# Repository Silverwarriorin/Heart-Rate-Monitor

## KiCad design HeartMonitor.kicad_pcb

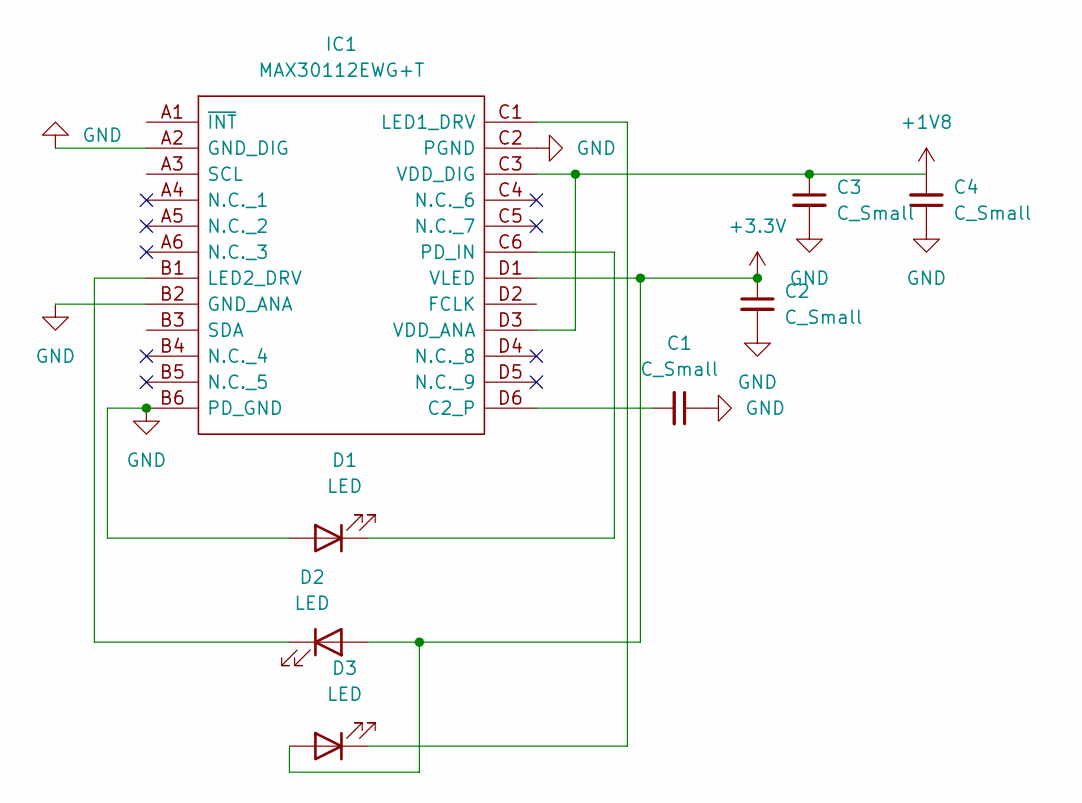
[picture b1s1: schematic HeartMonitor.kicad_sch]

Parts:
C1, C2, C3, C4: C_Small; C_0603_1608Metric_Pad1.08x0.95mm_HandSolder
D1, D2, D3: LED; D_0201_0603Metric
IC1: MAX30112EWG+T; BGA24C40P6X4_277X197X69; Mouser Part Number 700-MAX30112EWG+T

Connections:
+1V8: C3.1, C4.2, IC1.C3 (VDD_DIG), IC1.D3 (VDD_ANA)
+3V3: C2.1, D2.2 (A), D3.2 (A), IC1.D1 (VLED)
GND: C1.1, C2.2, C3.2, C4.1, D1.2 (A), IC1.A2 (GND_DIG), IC1.B2 (GND_ANA), IC1.B6 (PD_GND), IC1.C2 (PGND)
unnamed: D2.1 (K), IC1.B1 (LED2_DRV)
unnamed: D3.1 (K), IC1.C1 (LED1_DRV)
unnamed: D1.1 (K), IC1.C6 (PD_IN)
unnamed: C1.2, IC1.D6 (C2_P)

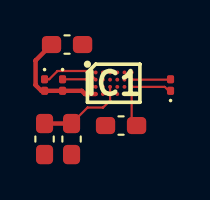
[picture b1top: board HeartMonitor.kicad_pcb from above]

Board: 2 copper layers, 8 parts (0 on the bottom side), 7 nets.

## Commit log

2022-02-18 Init Commit
